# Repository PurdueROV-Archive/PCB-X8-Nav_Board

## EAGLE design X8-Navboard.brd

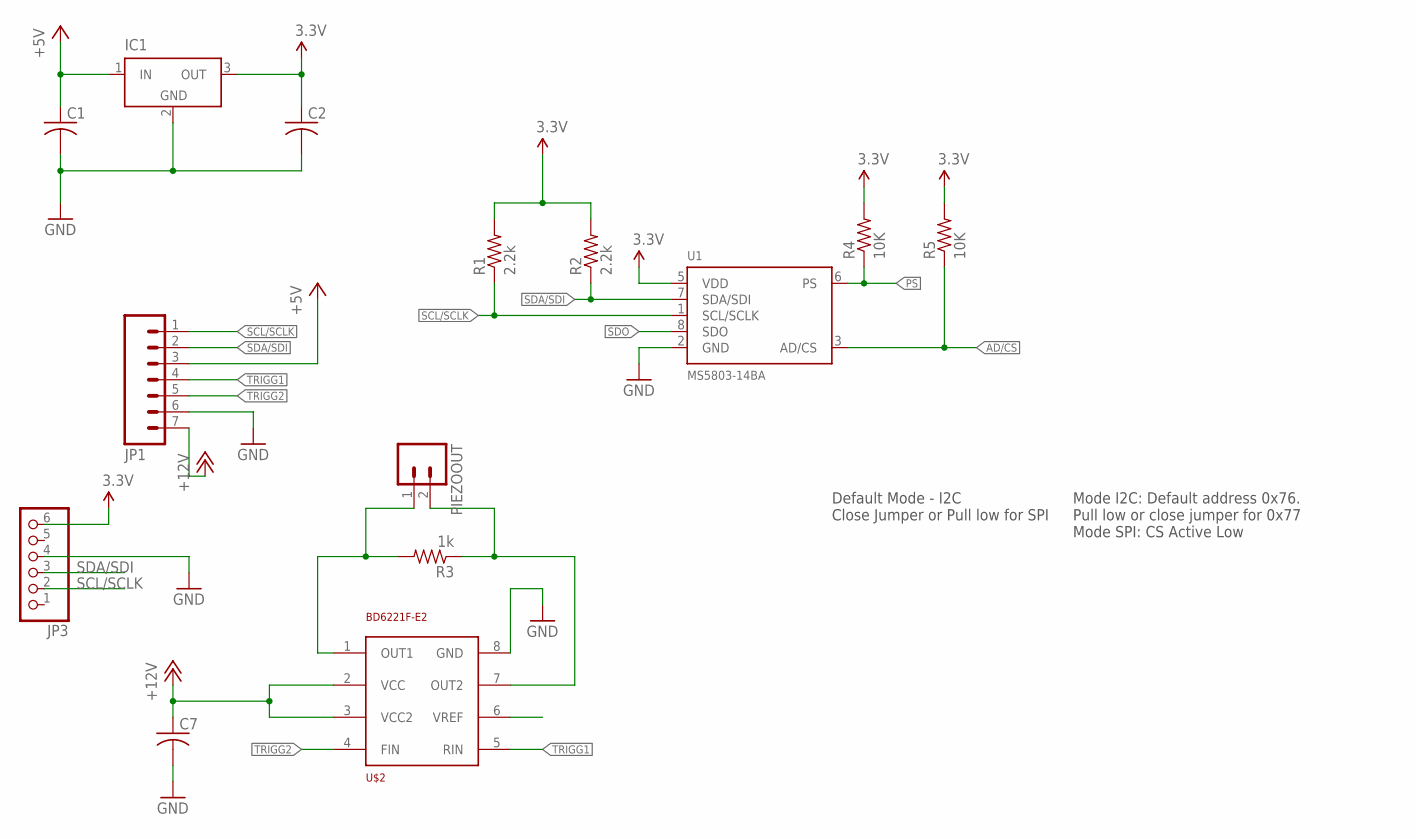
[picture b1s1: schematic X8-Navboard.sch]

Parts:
C1, C2, C7: C-USC0603; C0603
IC1: LT1129CST5; SOT223
JP1: M07; 1X07
JP3: PINHD-1X6; 1X06
PIEZOOUT: M02LOCK_LONGPADS; 1X02_LOCK_LONGPADS
R1, R2: 2.2k; 0603-RES
R3: 1k; 0603-RES
R4, R5: 10K; 0603-RES
U1: MS5803-14BA; MS5803
U$2: BD6221F-E2; SOIC8

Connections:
3.3V: C2.1, IC1.3 (OUT), JP3.6, R1.2, R2.2, R4.2, R5.2, U1.5 (VDD)
+5V: C1.1, IC1.1 (IN), JP1.3
+12V: C7.1, JP1.7, U$2.2 (VCC), U$2.3 (VCC2)
AD/CS: R5.1, U1.3 (AD/CS)
GND: C1.2, C2.2, C7.2, IC1.2 (GND), IC1.4 (GND), JP1.6, JP3.4, U1.2 (GND), U$2.8 (GND)
unnamed: PIEZOOUT.1, R3.2, U$2.1 (OUT1)
unnamed: PIEZOOUT.2, R3.1, U$2.7 (OUT2)
PS: R4.1, U1.6 (PS)
SCL/SCLK: JP1.1, JP3.2, R1.1, U1.1 (SCL/SCLK)
SDA/SDI: JP1.2, JP3.3, R2.1, U1.7 (SDA/SDI)
SDO: U1.8 (SDO)
TRIGG1: JP1.4, U$2.5 (RIN)
TRIGG2: JP1.5, U$2.4 (FIN)

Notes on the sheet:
Default Mode - I2C Close Jumper or Pull low for SPI
Mode I2C: Default address 0x76. Pull low or close jumper for 0x77 Mode SPI: CS Active Low

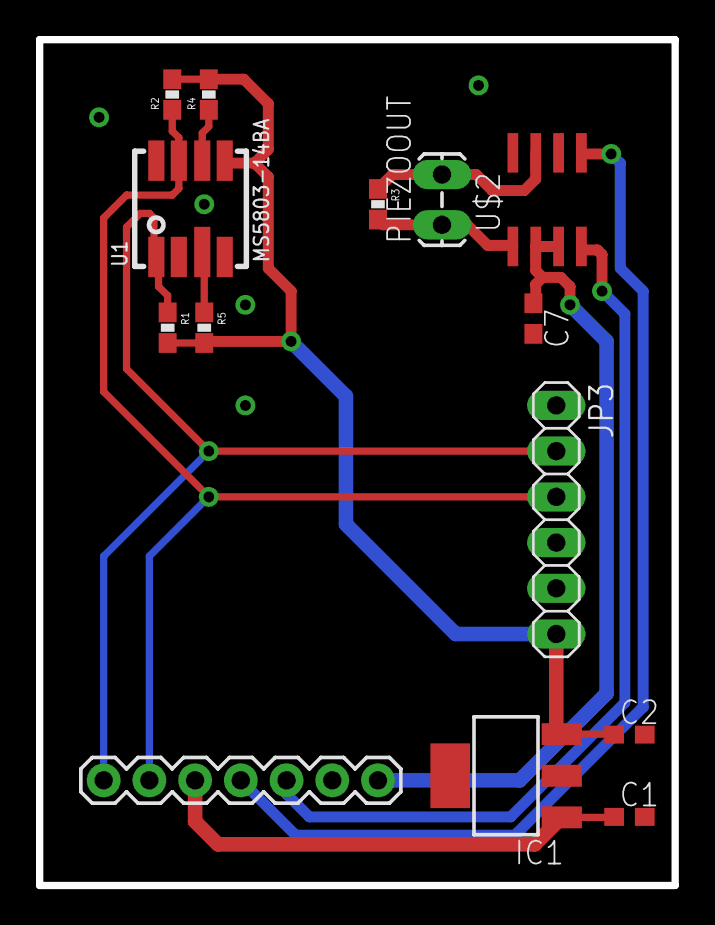
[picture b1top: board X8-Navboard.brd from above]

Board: 2 copper layers, 35.3 x 47.0 mm, 14 parts (0 on the bottom side), 12 nets.

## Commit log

2016-02-14 Finished the board layout for the nav board

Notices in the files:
parts and their libraries:
SparkFun-Connectors: Licensing: Creative Commons ShareAlike 4.0 International - https://creativecommons.org/licenses/by-sa/4.0
